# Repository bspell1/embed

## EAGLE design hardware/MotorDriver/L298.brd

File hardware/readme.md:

NrfPS2
=========

A wireless interface in a sardine can to a Playstation 2 controller.

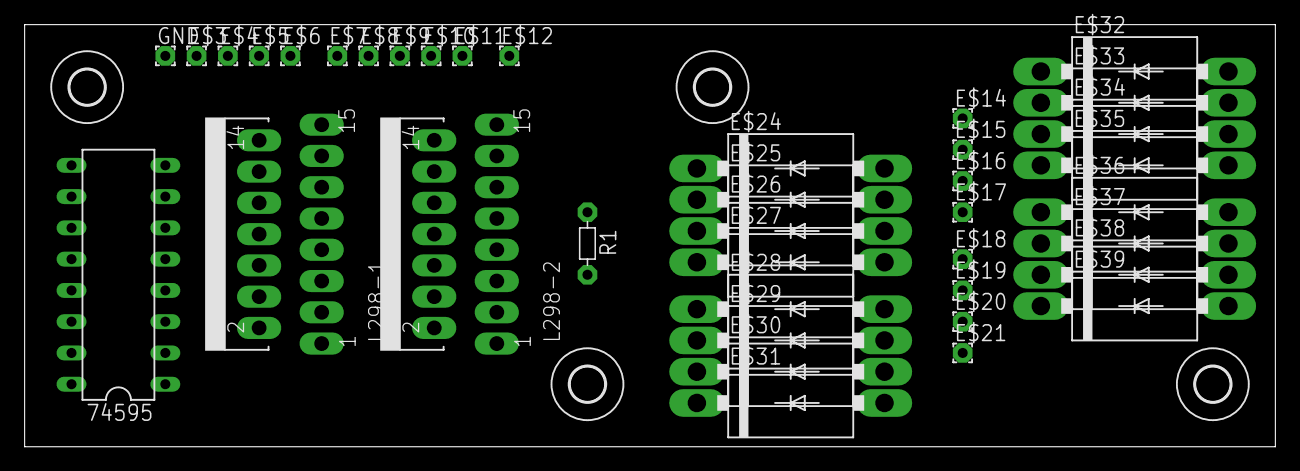
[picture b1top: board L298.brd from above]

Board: 2 copper layers, 101.6 x 34.3 mm, 43 parts (0 on the bottom side), 24 nets, no tracks yet.

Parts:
74595: 74595; DIL16
E$1, E$40, E$41, E$42: 2,8
E$3, E$4, E$5, E$6, E$7, E$8, E$9, E$10, E$11, E$12, E$14, E$15, E$16, E$17, E$18, E$19, E$20, E$21: 1,6/0,8
E$24, E$25, E$26, E$27, E$28, E$29, E$30, E$31, E$32, E$33, E$34, E$35, E$36, E$37, E$38, E$39: DO201-15
GND: 1,6/0,8
L298-1, L298-2: L298; MULTIWATT-15
R1: 10K; R-5

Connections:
S$1: 74595.8, 74595.13, E$7.1, E$32.A, E$33.A, E$34.A, E$35.A, E$36.A, E$37.A, E$38.A, E$39.A, GND.1, L298-1.1, L298-1.8, L298-1.15, L298-2.1, L298-2.8, L298-2.15
S$2: 74595.10, 74595.16, E$6.1, E$11.1, L298-1.9, L298-2.9, R1.1
S$3: 74595.11, E$3.1, E$8.1
S$4: 74595.12, E$4.1, E$9.1
S$5: 74595.14, E$5.1
S$6: 74595.9, E$10.1
S$7: E$14.1, E$24.A, E$32.C, L298-1.2
S$8: E$15.1, E$25.A, E$33.C, L298-1.3
S$9: E$12.1, E$24.C, E$25.C, E$26.C, E$27.C, E$28.C, E$29.C, E$30.C, E$31.C, L298-1.4, L298-2.4
S$10: 74595.15, L298-1.5
S$11: L298-1.6, L298-1.11, L298-2.6, L298-2.11, R1.2
S$12: 74595.1, L298-1.7
S$13: 74595.2, L298-1.10
S$14: 74595.3, L298-1.12
S$15: E$16.1, E$26.A, E$34.C, L298-1.13
S$16: E$17.1, E$27.A, E$35.C, L298-1.14
S$17: E$18.1, E$28.A, E$36.C, L298-2.2
S$18: E$19.1, E$29.A, E$37.C, L298-2.3
S$19: E$20.1, E$30.A, E$38.C, L298-2.13
S$20: E$21.1, E$31.A, E$39.C, L298-2.14
S$21: 74595.4, L298-2.5
S$22: 74595.5, L298-2.7
S$23: 74595.6, L298-2.10
S$24: 74595.7, L298-2.12

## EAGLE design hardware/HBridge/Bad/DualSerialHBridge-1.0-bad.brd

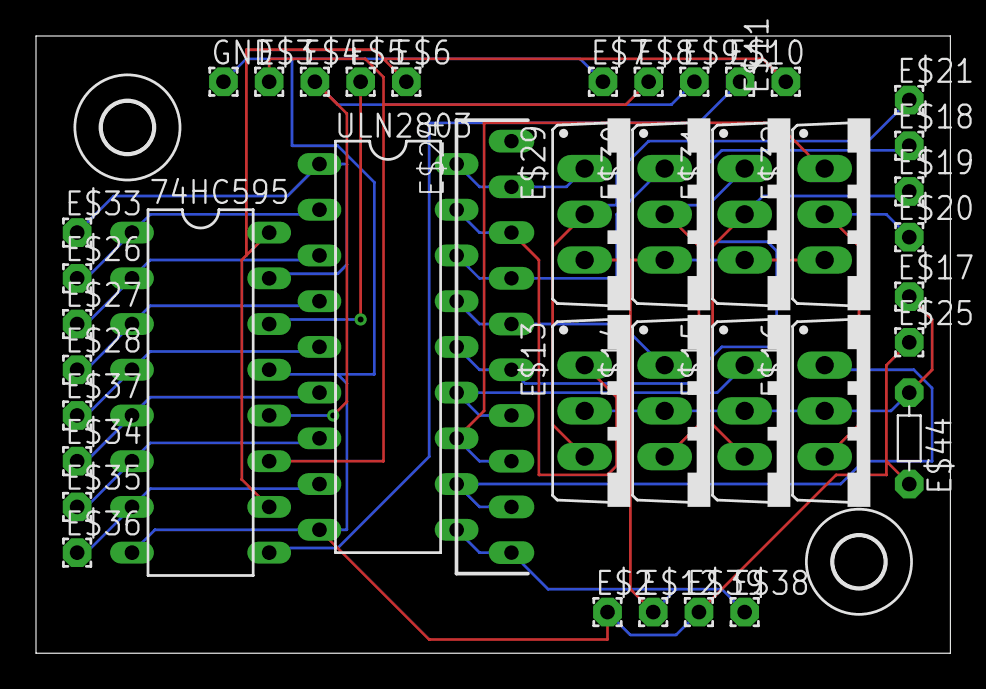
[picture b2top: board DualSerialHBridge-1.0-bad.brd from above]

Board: 2 copper layers, 50.8 x 34.3 mm, 42 parts (0 on the bottom side), 28 nets.

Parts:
74HC595: 74HC595; DIL16
E$2, E$3, E$4, E$5, E$6, E$7, E$8, E$9, E$10, E$11, E$12, E$17, E$18, E$19, E$20, E$21, E$25, E$26, E$27, E$28, E$33, E$34, E$35, E$36, E$37, E$38, E$39: 1,6/0,8
E$13, E$14, E$15, E$16, E$29, E$30, E$31, E$32: TO220V
E$24: SIP-10
E$40, E$42: 2,8
E$44: R-5
GND: 1,6/0,8
ULN2803: ULN2803; DIL18

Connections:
S$1: E$12.1, E$24.10, E$29.3, E$30.3, E$31.3, E$32.3, E$38.1, ULN2803.10
S$2: 74HC595.10, 74HC595.16, E$6.1, E$11.1
S$3: 74HC595.11, E$3.1, E$8.1
S$4: 74HC595.12, E$4.1, E$9.1
S$5: 74HC595.14, E$5.1
S$6: E$24.2, E$29.1, ULN2803.18
S$7: E$24.6, E$31.1, ULN2803.14
S$8: E$13.1, E$24.3, ULN2803.17
S$9: E$24.4, E$30.1, ULN2803.16
S$10: E$14.1, E$24.5, ULN2803.15
S$11: 74HC595.15, E$33.1, ULN2803.1
S$12: 74HC595.8, 74HC595.13, E$2.1, E$7.1, E$25.1, E$39.1, E$44.2, GND.1, ULN2803.9
S$13: E$15.1, E$24.7, ULN2803.13
S$14: E$24.8, E$32.1, ULN2803.12
S$15: E$16.1, E$24.9, ULN2803.11
S$16: 74HC595.1, E$26.1, ULN2803.2
S$17: 74HC595.2, E$27.1, ULN2803.3
S$18: 74HC595.3, E$28.1, ULN2803.4
S$19: 74HC595.4, E$37.1, ULN2803.5
S$20: 74HC595.5, E$34.1, ULN2803.6
S$21: 74HC595.6, E$35.1, ULN2803.7
S$22: 74HC595.9, E$10.1
S$23: 74HC595.7, E$36.1, ULN2803.8
S$24: E$13.2, E$14.2, E$15.2, E$16.2, E$17.1, E$44.1
S$25: E$13.3, E$21.1, E$29.2
S$26: E$14.3, E$18.1, E$30.2
S$27: E$15.3, E$19.1, E$31.2
S$28: E$16.3, E$20.1, E$32.2

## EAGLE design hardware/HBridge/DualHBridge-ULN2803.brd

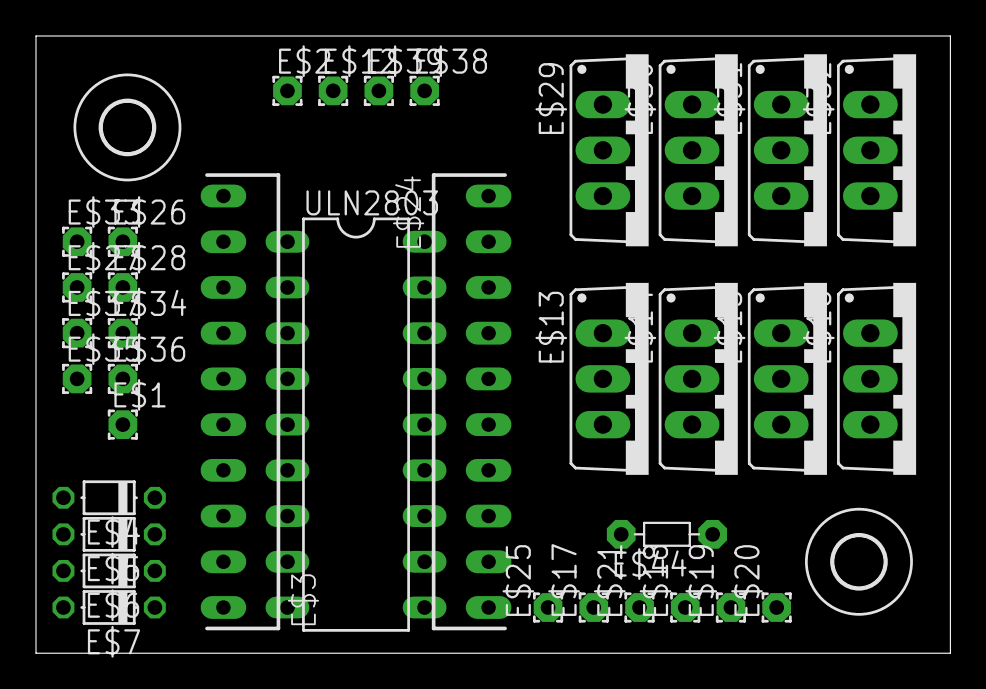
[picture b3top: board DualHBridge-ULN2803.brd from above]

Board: 2 copper layers, 50.8 x 34.3 mm, 37 parts (0 on the bottom side), 27 nets, no tracks yet.

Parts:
E$1, E$2, E$12, E$17, E$18, E$19, E$20, E$21, E$25, E$26, E$27, E$28, E$33, E$34, E$35, E$36, E$37, E$38, E$39: 1,6/0,8
E$3, E$24: SIP-10
E$4, E$5, E$6, E$7: D-5
E$13, E$14, E$15, E$16, E$29, E$30, E$31, E$32: TO220V
E$40, E$42: 2,8
E$44: R-5
ULN2803: ULN2803; DIL18

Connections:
S$1: E$12.1, E$24.10, E$29.3, E$30.3, E$31.3, E$32.3, E$38.1, ULN2803.10
S$2: E$3.7, E$26.1
S$3: E$3.8, E$4.C, ULN2803.2
S$4: E$3.6, E$5.C, ULN2803.4
S$5: E$3.4, E$6.C, ULN2803.6
S$6: E$24.2, E$29.1, ULN2803.18
S$7: E$24.6, E$31.1, ULN2803.14
S$8: E$13.1, E$24.3, ULN2803.17
S$9: E$24.4, E$30.1, ULN2803.16
S$10: E$14.1, E$24.5, ULN2803.15
S$11: E$4.A, E$33.1, ULN2803.1
S$12: E$1.1, E$2.1, E$25.1, E$39.1, E$44.2, ULN2803.9
S$13: E$15.1, E$24.7, ULN2803.13
S$14: E$24.8, E$32.1, ULN2803.12
S$15: E$16.1, E$24.9, ULN2803.11
S$16: E$3.5, E$28.1
S$17: E$5.A, E$27.1, ULN2803.3
S$18: E$3.3, E$34.1
S$19: E$6.A, E$37.1, ULN2803.5
S$20: E$3.1, E$36.1
S$21: E$7.A, E$35.1, ULN2803.7
S$22: E$3.2, E$7.C, ULN2803.8
S$24: E$13.3, E$14.3, E$15.3, E$16.3, E$17.1, E$44.1
S$25: E$13.2, E$21.1, E$29.2
S$26: E$14.2, E$18.1, E$30.2
S$27: E$15.2, E$19.1, E$31.2
S$28: E$16.2, E$20.1, E$32.2

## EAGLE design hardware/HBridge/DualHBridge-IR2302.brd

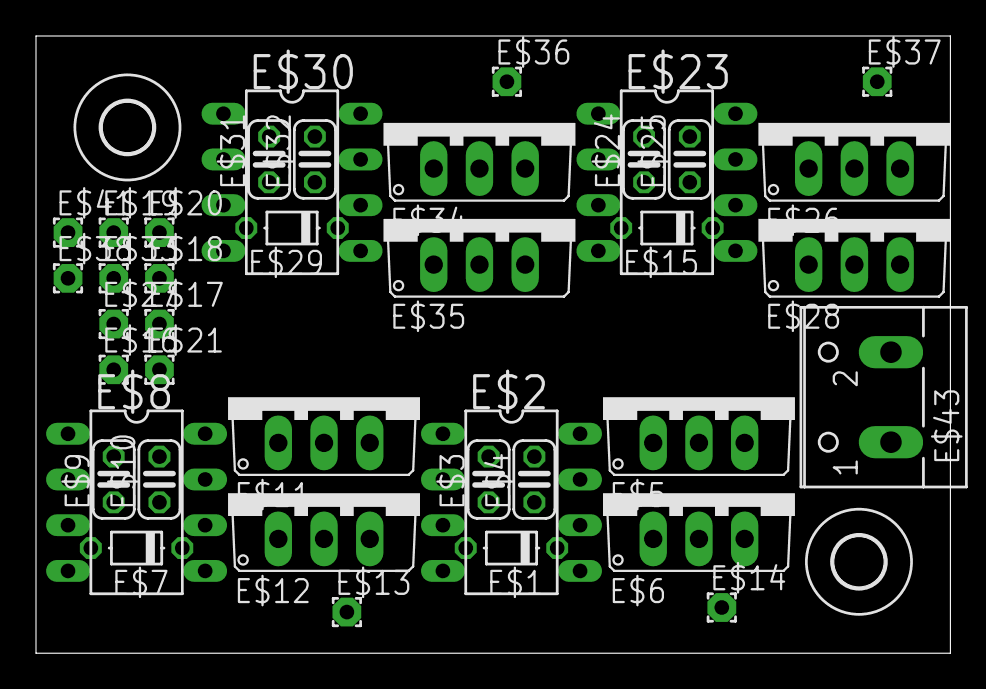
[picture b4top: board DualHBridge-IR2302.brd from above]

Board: 2 copper layers, 50.8 x 34.3 mm, 41 parts (0 on the bottom side), 26 nets, no tracks yet.

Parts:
E$1, E$7, E$15, E$29: D-5
E$2, E$8, E$23, E$30: DIL8
E$3, E$4, E$9, E$10, E$24, E$25, E$31, E$32: C025-024X044
E$5, E$6, E$11, E$12, E$26, E$28, E$34, E$35: TO220V
E$13, E$14, E$16, E$17, E$18, E$19, E$20, E$21, E$27, E$33, E$36, E$37, E$38, E$41: 1,6/0,8
E$40, E$42: 2,8
E$43: W237-102

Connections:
S$1: E$1.A, E$2.1, E$3.2, E$5.2, E$7.A, E$8.1, E$9.2, E$11.2, E$15.A, E$23.1, E$24.2, E$26.2, E$29.A, E$30.1, E$31.2, E$34.2, E$43.2
S$2: E$2.4, E$3.1, E$6.3, E$8.4, E$9.1, E$12.3, E$23.4, E$24.1, E$28.3, E$30.4, E$31.1, E$35.3, E$38.1, E$43.1
S$3: E$19.1, E$30.2
S$4: E$1.C, E$2.8, E$4.2
S$5: E$2.2, E$16.1
S$6: E$2.6, E$4.1, E$5.3, E$6.2, E$14.1
S$7: E$2.7, E$5.1
S$8: E$2.5, E$6.1
S$10: E$20.1, E$30.3
S$11: E$23.2, E$33.1
S$12: E$7.C, E$8.8, E$10.2
S$13: E$2.3, E$21.1
S$14: E$8.6, E$10.1, E$11.3, E$12.2, E$13.1
S$15: E$8.7, E$11.1
S$17: E$8.2, E$27.1
S$18: E$15.C, E$23.8, E$25.2
S$20: E$23.6, E$25.1, E$26.3, E$28.2, E$37.1
S$21: E$23.7, E$26.1
S$22: E$23.5, E$28.1
S$25: E$29.C, E$30.8, E$32.2
S$27: E$30.6, E$32.1, E$34.3, E$35.2, E$36.1
S$28: E$30.7, E$34.1
S$29: E$30.5, E$35.1
S$31: E$18.1, E$23.3
S$32: E$8.3, E$17.1
S$33: E$8.5, E$12.1

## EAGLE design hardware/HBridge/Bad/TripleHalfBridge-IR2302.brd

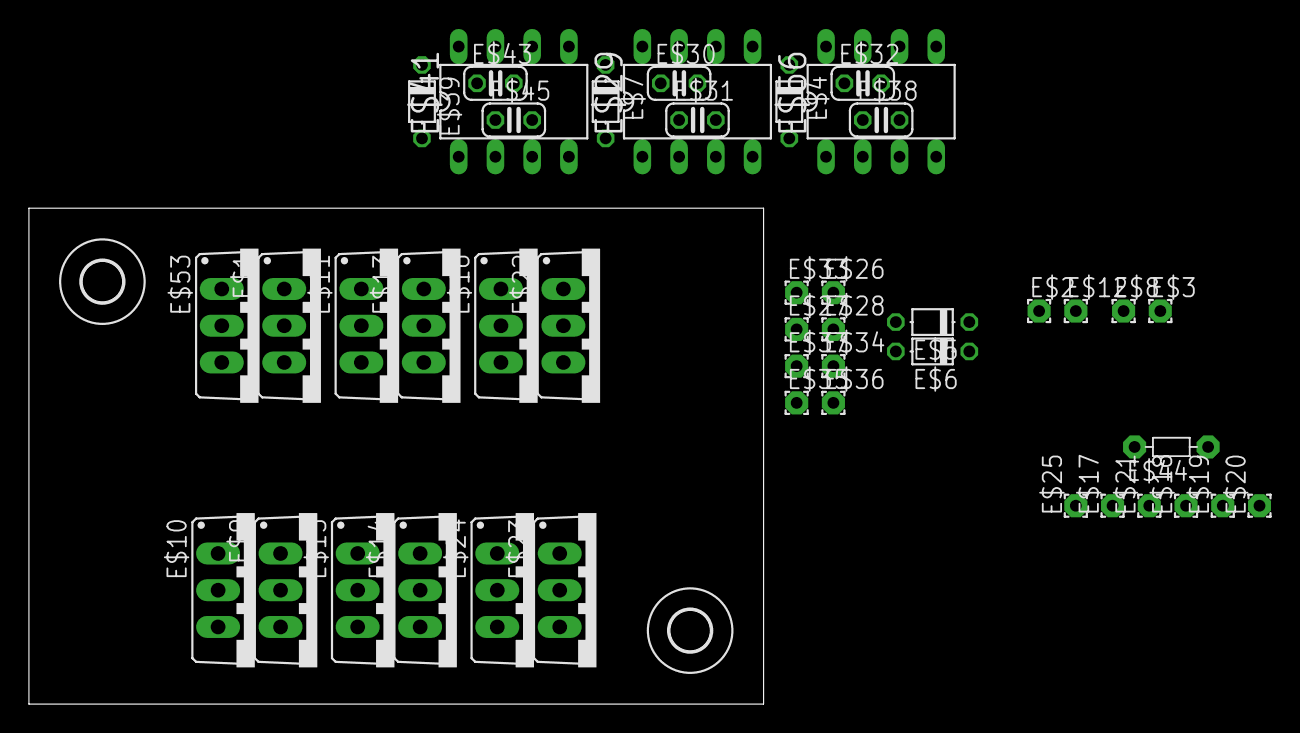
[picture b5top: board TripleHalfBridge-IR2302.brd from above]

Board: 2 copper layers, 50.8 x 34.3 mm, 47 parts (0 on the bottom side), 10 nets, no tracks yet.

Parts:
E$1, E$9, E$10, E$11, E$13, E$14, E$15, E$16, E$22, E$23, E$24, E$53: TO220V
E$2, E$3, E$8, E$12, E$17, E$18, E$19, E$20, E$21, E$25, E$26, E$27, E$28, E$33, E$34, E$35, E$36, E$37: 1,6/0,8
E$4, E$5, E$6, E$7, E$39: D-5
E$29, E$41, E$56: DIL8
E$30, E$31, E$32, E$38, E$43, E$45: C025-024X044
E$40, E$42: 2,8
E$44: R-5

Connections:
S$1: E$1.3, E$53.3
S$6: E$1.2, E$53.2
S$7: E$1.1, E$53.1
S$8: E$9.1, E$10.1
S$9: E$9.2, E$10.2
S$11: E$25.1, E$44.2
S$24: E$17.1, E$44.1
S$25: E$9.3, E$10.3
S$29: E$11.1, E$13.1
S$30: E$16.1, E$22.1

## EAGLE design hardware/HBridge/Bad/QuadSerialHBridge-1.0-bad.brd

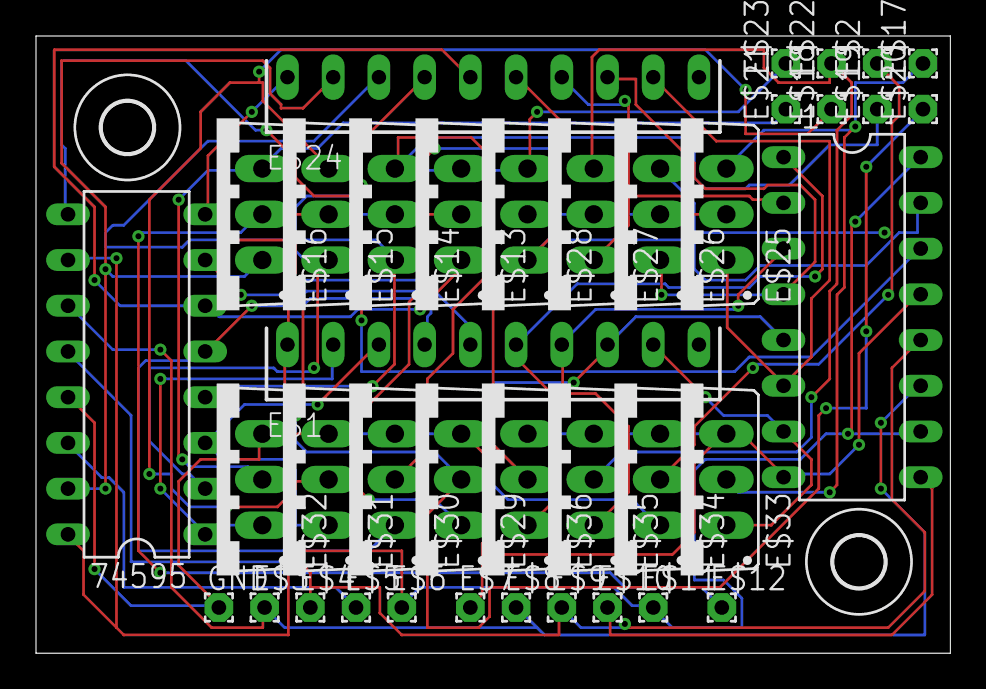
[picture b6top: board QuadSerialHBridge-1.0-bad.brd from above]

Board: 2 copper layers, 50.8 x 34.3 mm, 41 parts (0 on the bottom side), 32 nets.

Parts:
1, 74595: 74595; DIL16
E$1, E$24: SIP-10
E$2, E$3, E$4, E$5, E$6, E$7, E$8, E$9, E$10, E$11, E$12, E$17, E$18, E$19, E$20, E$21, E$22, E$23: 1,6/0,8
E$13, E$14, E$15, E$16, E$25, E$26, E$27, E$28, E$29, E$30, E$31, E$32, E$33, E$34, E$35, E$36: TO220V
E$40, E$42: 2,8
GND: 1,6/0,8

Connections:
S$1: 74595.1, E$1.2, E$32.1
S$2: 1.10, 1.16, 74595.10, 74595.16, E$6.1, E$11.1
S$3: 1.11, 74595.11, E$3.1, E$8.1
S$4: 1.12, 74595.12, E$4.1, E$9.1
S$5: 74595.14, E$5.1
S$6: 1.14, 74595.9
S$7: 1.15, E$24.6, E$28.1
S$8: 74595.2, E$15.1, E$24.3
S$9: E$12.1, E$13.2, E$14.2, E$15.2, E$16.2, E$25.2, E$26.2, E$27.2, E$28.2
S$10: 74595.15, E$16.1, E$24.2
S$11: 74595.4, E$14.1, E$24.4
S$12: 1.8, 1.13, 74595.8, 74595.13, E$1.1, E$7.1, E$24.1, E$29.3, E$30.3, E$31.3, E$32.3, E$33.3, E$34.3, E$35.3, E$36.3, GND.1
S$13: 1.2, E$24.7, E$27.1
S$14: 1.4, E$24.8, E$26.1
S$15: 1.6, E$24.9, E$25.1
S$16: 1.1, E$1.6, E$36.1
S$17: 1.3, E$1.7, E$35.1
S$18: 1.5, E$1.8, E$34.1
S$19: 74595.3, E$1.3, E$31.1
S$20: 74595.5, E$1.4, E$30.1
S$21: 1.7, E$1.9, E$33.1
S$22: 1.9, E$10.1
S$23: 74595.6, E$13.1, E$24.5
S$24: 74595.7, E$1.5, E$29.1
S$25: E$23.1, E$28.3, E$36.2
S$26: E$22.1, E$27.3, E$35.2
S$27: E$2.1, E$26.3, E$34.2
S$28: E$16.3, E$21.1, E$32.2
S$29: E$15.3, E$18.1, E$31.2
S$30: E$14.3, E$19.1, E$30.2
S$31: E$13.3, E$20.1, E$29.2
S$32: E$17.1, E$25.3, E$33.2

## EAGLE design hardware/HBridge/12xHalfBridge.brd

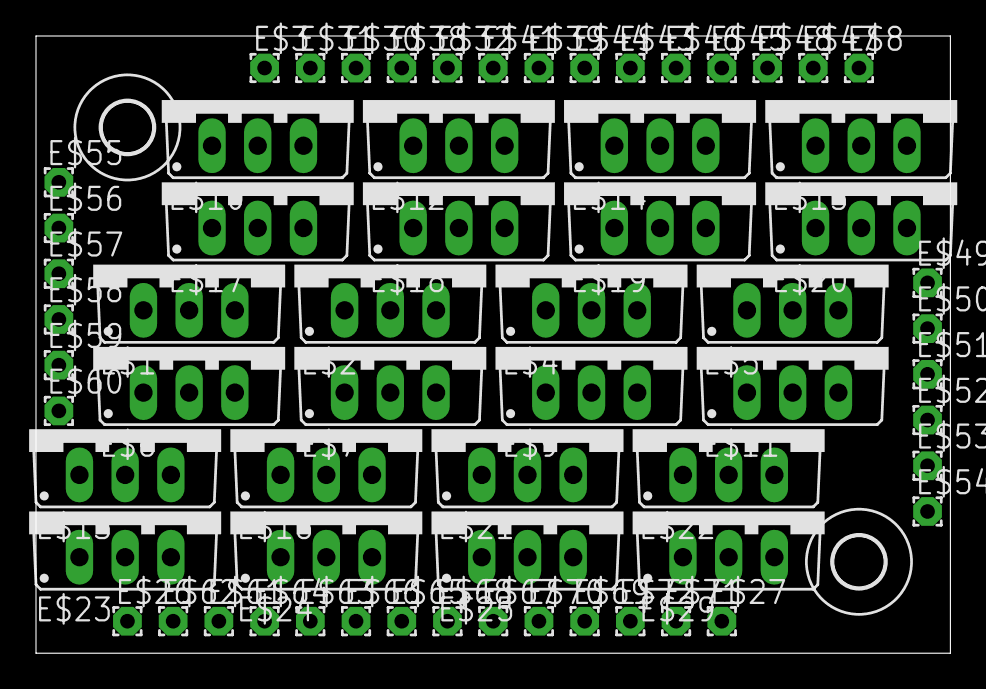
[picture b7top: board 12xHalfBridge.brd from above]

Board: 2 copper layers, 50.8 x 34.3 mm, 66 parts (0 on the bottom side), 38 nets, no tracks yet.

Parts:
E$1, E$2, E$4, E$5, E$6, E$7, E$9, E$10, E$11, E$12, E$13, E$14, E$15, E$16, E$17, E$18, E$19, E$20, E$21, E$22, E$23, E$24, E$25, E$29: TO220V
E$3, E$8, E$26, E$27, E$30, E$31, E$32, E$38, E$39, E$41, E$43, E$44, E$45, E$46, E$47, E$48, E$49, E$50, E$51, E$52, E$53, E$54, E$55, E$56, E$57, E$58, E$59, E$60, E$61, E$62, E$63, E$64, E$65, E$66, E$67, E$68, E$69, E$70, E$71, E$72: 1,6/0,8
E$40, E$42: 2,8

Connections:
S$1: E$17.1, E$30.1
S$2: E$10.1, E$31.1
S$3: E$12.1, E$32.1
S$4: E$2.1, E$39.1
S$5: E$19.1, E$43.1
S$6: E$15.1, E$45.1
S$7: E$5.1, E$47.1
S$8: E$9.2, E$14.3, E$49.1
S$9: E$19.3, E$21.2, E$50.1
S$10: E$4.3, E$25.2, E$51.1
S$11: E$11.2, E$15.3, E$52.1
S$12: E$20.3, E$22.2, E$53.1
S$13: E$5.3, E$29.2, E$54.1
S$14: E$6.2, E$10.3, E$55.1
S$15: E$13.2, E$17.3, E$56.1
S$16: E$1.1, E$38.1
S$17: E$1.3, E$23.2, E$57.1
S$18: E$18.1, E$41.1
S$19: E$7.2, E$12.3, E$58.1
S$20: E$6.1, E$62.1
S$21: E$16.2, E$18.3, E$59.1
S$22: E$2.3, E$24.2, E$60.1
S$23: E$13.1, E$61.1
S$24: E$7.1, E$63.1
S$25: E$24.1, E$65.1
S$26: E$21.1, E$67.1
S$27: E$11.1, E$69.1
S$28: E$29.1, E$71.1
S$29: E$23.1, E$64.1
S$30: E$16.1, E$66.1
S$31: E$9.1, E$68.1
S$32: E$25.1, E$70.1
S$33: E$22.1, E$72.1
S$34: E$14.1, E$44.1
S$35: E$4.1, E$46.1
S$36: E$20.1, E$48.1
S$37: E$1.2, E$2.2, E$3.1, E$4.2, E$5.2, E$8.1, E$10.2, E$12.2, E$14.2, E$15.2, E$17.2, E$18.2, E$19.2, E$20.2
S$38: E$6.3, E$7.3, E$9.3, E$11.3, E$13.3, E$16.3, E$21.3, E$22.3, E$23.3, E$24.3, E$25.3, E$26.1, E$27.1, E$29.3

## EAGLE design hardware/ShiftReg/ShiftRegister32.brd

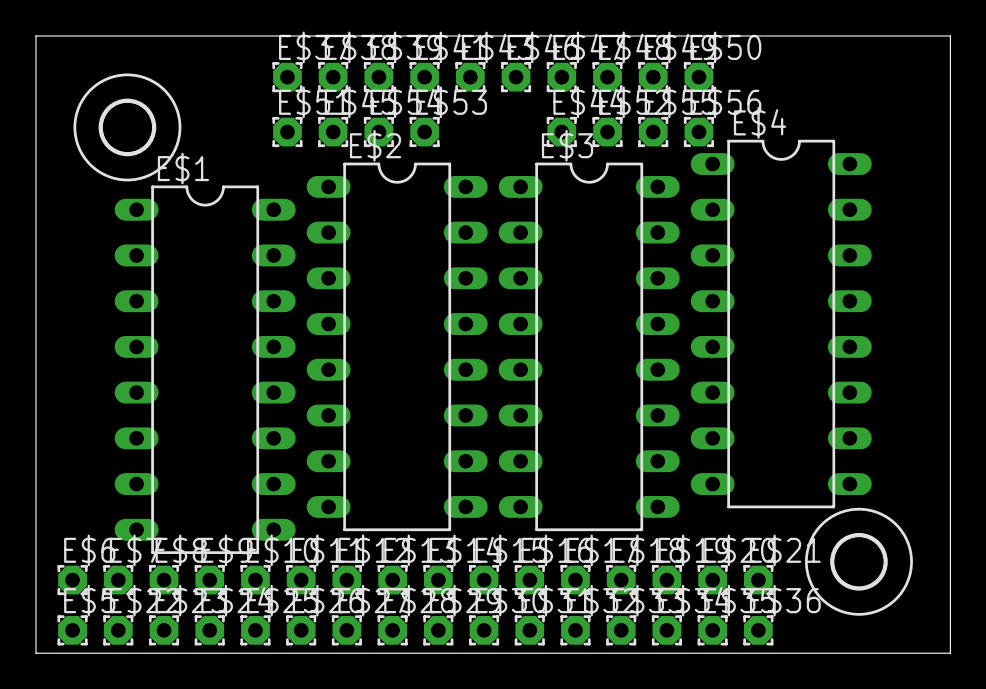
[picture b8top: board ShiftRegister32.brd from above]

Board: 2 copper layers, 50.8 x 34.3 mm, 56 parts (0 on the bottom side), 49 nets, no tracks yet.

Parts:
E$1, E$2, E$3, E$4: 74HC595; DIL16
E$5, E$6, E$7, E$8, E$9, E$10, E$11, E$12, E$13, E$14, E$15, E$16, E$17, E$18, E$19, E$20, E$21, E$22, E$23, E$24, E$25, E$26, E$27, E$28, E$29, E$30, E$31, E$32, E$33, E$34, E$35, E$36, E$37, E$38, E$39, E$41, E$43, E$44, E$45, E$46, E$47, E$48, E$49, E$50, E$51, E$52, E$53, E$54, E$55, E$56: 1,6/0,8
E$40, E$42: 2,8

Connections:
S$1: E$1.8, E$2.8, E$3.8, E$4.8, E$37.1, E$46.1
S$2: E$1.13, E$51.1
S$3: E$1.11, E$2.11, E$3.11, E$4.11, E$38.1, E$47.1
S$4: E$1.12, E$2.12, E$3.12, E$4.12, E$39.1, E$48.1
S$5: E$1.14, E$41.1
S$6: E$1.9, E$2.14
S$7: E$2.9, E$3.14
S$8: E$3.9, E$4.14
S$9: E$1.16, E$2.16, E$3.16, E$4.16, E$43.1, E$50.1
S$10: E$4.9, E$49.1
S$11: E$2.13, E$45.1
S$12: E$3.13, E$54.1
S$13: E$4.13, E$53.1
S$14: E$1.10, E$44.1
S$15: E$2.10, E$52.1
S$16: E$3.10, E$55.1
S$17: E$4.10, E$56.1
S$18: E$1.15, E$6.1
S$19: E$2.15, E$14.1
S$20: E$3.15, E$5.1
S$21: E$4.15, E$29.1
S$22: E$1.1, E$7.1
S$23: E$1.2, E$8.1
S$24: E$1.3, E$9.1
S$25: E$1.4, E$10.1
S$26: E$1.5, E$11.1
S$27: E$1.6, E$12.1
S$28: E$1.7, E$13.1
S$29: E$2.1, E$15.1
S$30: E$2.2, E$16.1
S$31: E$2.3, E$17.1
S$32: E$2.4, E$18.1
S$33: E$2.5, E$19.1
S$34: E$2.6, E$20.1
S$35: E$2.7, E$21.1
S$36: E$3.1, E$22.1
S$37: E$3.2, E$23.1
S$38: E$3.3, E$24.1
S$39: E$3.4, E$25.1
S$40: E$3.5, E$26.1
S$41: E$3.6, E$27.1
S$42: E$3.7, E$28.1
S$43: E$4.1, E$30.1
S$44: E$4.2, E$31.1
S$45: E$4.3, E$32.1
S$46: E$4.4, E$33.1
S$47: E$4.5, E$34.1
S$48: E$4.6, E$35.1
S$49: E$4.7, E$36.1

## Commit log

2013-04-25 Initial revision
2013-04-26 Added initial version of avrtest
2013-04-28 More AVR work
2013-04-29 Fleshed out TLC5940 test implementation
2013-04-30 Corrected TLC5940 BLANK pulse, reorganized pins
2013-04-30 Refactored TLC5940 and digital I/O
2013-04-30 TLC5940 breakthrough - fixed byte ordering problem
2013-04-30 Refactored the TLC5940 greyscale buffer representation to optimize clocking it into the unit
2013-05-01 Began working on I2C interface
2013-05-02 Testing with SX1509
2013-05-02 I2C refinements
2013-05-02 Modified linux I2C to set slave address during each transfer
2013-05-02 I2C cleanup and added support for combined read/write transactions
2013-05-02 Fixed problem with I2C slave addresses not being shifted
2013-05-02 Corrected integer signed type
2013-05-03 Added display to camera app
2013-05-03 Began work on the SX1509 interface
2013-05-06 More SX1509 work
2013-05-06 Began working on protocol module
2013-05-06 More protocol work
2013-05-06 Cleaned up all interfaces, implemented stepper motor module, added configuration parameters
2013-05-08 Initial working version of motor framework
2013-05-08 Motor testing successful; modified 5940 and motor driver to use the same clock, freeing up the 16-bit clock 1
2013-05-08 Fleshed out SX1509 interface, cleanup
2013-05-08 Changed casing on all macros; refactored uart into separate module
2013-05-08 Refactored the protocol implementation to run async and validate message signatures
2013-05-08 Corrected timer interrupt name
2013-05-09 Added locomoto to Mono lab
2013-05-09 Added device address to eeprom
2013-05-09 Added loco address protocol
2013-05-09 Revised NPi stepper framework, added LocoMoto driver
2013-05-13 Fixed buffer counting problem in protocol; began working on tracking down buffer overrun in motor driver/I2C
2013-05-13 Fixed UART instability by reducing baud rate to 57600
2013-05-13 Added volatile to all global accessors from ISRs; added keyboard interface to motors
2013-05-14 Implemented simple keyboard motor input
2013-05-14 Removed support for programming over arduino serial
2013-05-22 Initial work on wiichuk
2013-05-22 Refactored I2C to use a preallocated buffer for transfers
2013-05-23 Cleaned up transports and added multi-byte async UART operations
2013-05-23 Modified UART string receive to consume the null terminator
2013-05-23 Added support for delimited UART reads/writes
2013-05-24 Straightened out UART sync/async interface
2013-05-24 Added async support to SPI/I2C interfaces
2013-05-28 Began working on debug library
2013-05-28 Project reorganization
2013-05-29 Initial pass of WiiChuk remote
2013-06-04 More WiiChuk work
2013-06-04 Added compiler/linker options to remove unused functions
2013-06-04 Added debug module with the ability to disable the WDT after an assert reboot
2013-06-04 Modified UART string formatter to allow arbitrary length messages
2013-06-06 Functioning WiiChuk!
2013-06-06 Modified the WiiChuk to read its address from EEPROM
2013-06-07 Another working version of WiiChuk, with EEPROM preservation when flashing and corrected EEPROM reads
2013-06-12 Corrected PinSetPullUp and added PinSetTriState for I/O pin configuration
2013-06-12 Initial version of shift register API
2013-06-14 Initial version of locomoto mark 2, with shift registers
2013-06-14 Simplified the shift register interface for nibbles
2013-06-14 Initial version of the HCSR04 range finder
2013-06-15 Working locomoto!
2013-06-17 Modified the stepper to support graceful shutdown + in-flight step/delay change and turn off all magnets when idle
2013-06-18 Refactored base make to support custom fuses
    Reorganized locomoto pins
    Modified shift register to write atomically
    Reorganized source directories
2013-06-18 Cleaned up UartPing and added linux support
2013-06-19 Refactored NPi out of the lab project
    Added support for default linux serial port to uartping
2013-06-19 Added the shift register dance program
2013-06-20 Simplified stepper event handler
    Modified wiichuk pair to filter buttons when receiving calibration requests
2013-06-21 Refactored and commented the stepper driver
2013-06-25 Locomoto refactoring
    Added support for a second shift register for digital output in locomoto
2013-06-26 Added support for firing a solenoid to the right z-button
2013-07-21 Added stepper test
    Added configurable max RPM
    Added threshold RPM, to avoid burning up motor driver
    Added new motors
2013-07-29 Added minimum RPM configuration to stepper motor and corrected the shift register count in locomoto - working prototype
2013-10-02 Fixed TLC5940 bugs
2013-11-04 Fixed TLC5940 PWM counter bug
2013-11-11 Added MPU-6050 CLR interface
2013-11-11 Added quopter project, PID controller framework, quadcopter thrust controller
2013-11-12 Added missing rotor channel initialization
2013-11-12 Reset the lab for UART testing
2013-11-12 Added the MPU-6050 interface
2013-11-12 MPU-6050 testing, initial version of hovering quopter
2013-11-13 Quopter stability changes
2013-11-14 TLC5940 last ditch
2013-11-14 Initial pass of the PWM bit banger
2013-11-15 Modified pwmbang to use 100kHz timer for a total of 100 servo positions
2013-11-15 Corrected 100kHz timer prescalar calculation
2013-11-15 Modified the PWM banger not to pulse channels with duty 0
2013-11-18 Added ESC calibration and resurrected the TLC5940
2013-11-19 Added complementary filter tests to the lab for the MPU, fighting Mono floating point bugs
2013-11-19 Implemented quopter MPU and filtering. Added receive capabilities to nrf24.
2013-11-20 Initial version of the untuned balancing quopter
2013-11-20 Initial pass of Nrf24Echo and ChukEcho programs
2013-11-20 Fleshed out the NrfEcho and ChukEcho utilities
2013-11-21 Added clamp/map framework. Quopter tuning.
2013-11-22 Hovering quopter
2013-11-22 TLC5940 cleanup for configurable clocks, testing MapClamp
2013-11-22 Initial wiichuk integration
2013-11-23 Fixed TLC5940 bugs for servos, temporarily disabled quopter communications
2013-11-24 Fixed NRF24 bugs, added disable-ack validation rule, implemented sample chuk relay transceiver
2013-11-25 Added synchronous waits to Nrf24PowerOn to finish up existing transmissions and flush the receive queue. Added quopter telemetrics.
2013-11-25 Began working on lab for servo PWM using clock 1
2013-11-26 Timer1-based servo motor pair lab
2013-11-26 Initial version of working input/sensor/telemetrics/output quopter at ~59Hz
2013-11-26 Implemented a quopter telemetrics program
2013-11-26 Corrected roll/pitch angle calculation for telemetrics
2013-11-26 Corrected quopecho counter initialization
2013-11-26 Removed chuk accelerometer readings and modified the rotor thrust to use integer calculations to bring cycle time above 100Hz
2013-11-27 Main loop cleanup. Modified roll/pitch sensors and input to be measured in angles and converted to thrust after control. Modified the quopter only to toggle the LED when the controller is on.
2013-11-27 Initial pass of the bomb bay, relocated SS/BLANK pins to enable timer1 for the bomb bay servos
2013-11-27 Moved the blank pin to D3, so it is on the same side of the board as the other pins, and so as not to lose another ADC pin
2013-12-11 Added quopter chuk input rotor control, ready for hover test
2013-12-12 Quopter tuning, failed to achieve liftoff
2013-12-12 Initial pass of 3-phase controller lab
2014-02-04 Quopter thrust fine tuning
2014-02-09 Working PSX lab
2014-02-17 Working PSX pad program; added UART message echo program
2014-02-17 Implemented the PSX echo tool
2014-02-17 Modified psxpad to zero out the analog joystick samples if the controller reports digital-only mode
2014-02-17 Removed unnecessary interrupt poll in NRF24 event handlers
2014-02-18 Migrated the locomoto to the PSX control pad
2014-02-18 Migrated the quopter to the PSX control pad
2014-02-26 Working psxpad PCB
2014-03-02 Working locomoto with psx
2014-03-27 H-Bridge 2.0
2014-03-31 Working shiftreg/opamp MOSFET bridge driver, AVR timer with frequency and duty cycle
2014-04-01 Migrated LocoMoto control away from Raspberry PI. Implemented AVR nrfping.
2014-05-14 New dual H-Bridge design, with shoot-through protection
2014-05-15 Added the 32-bit shift register bank
2014-05-22 Added the 12x half bridge board
2014-05-28 Added the IR2302-based dual bridge board
2014-06-18 Working MOSFET + IR2302 AVR locomoto
2014-07-01 Build cleanup + locomoto with PID throttle controller
2014-07-10 Initial pass of 7-segment framework
2014-07-14 Renamed the dump-size build target
2014-07-15 7-segment framework refactoring
2016-10-05 osx conversion
